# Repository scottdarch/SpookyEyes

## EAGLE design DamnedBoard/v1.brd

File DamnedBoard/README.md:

# Birds-of-the-Damned (say it in a spooky voice)

The hardware designs are provided under (Creative Commons Attribution-ShareAlike 3.0)[https://creativecommons.org/licenses/by-sa/3.0/legalcode].

The firmware is provided under Apache 2.0.

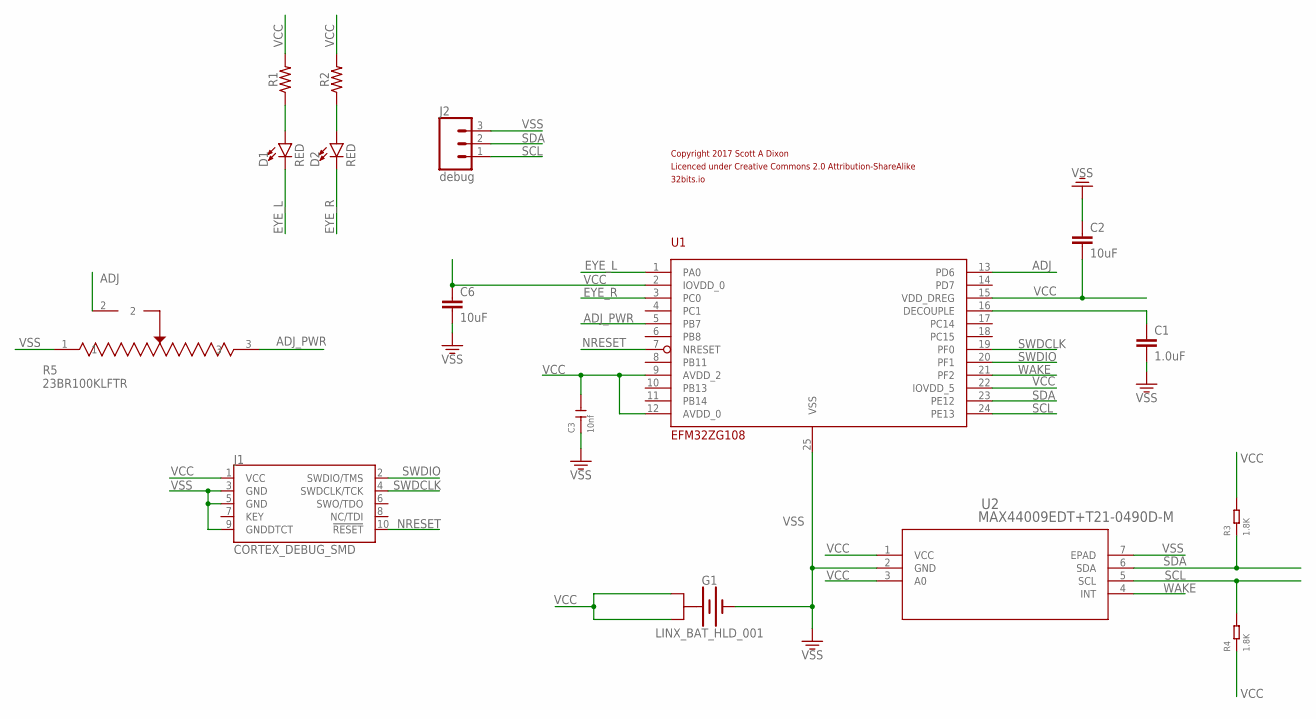
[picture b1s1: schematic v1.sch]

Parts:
C1: 1.0uF; 0603
C2, C6: 10uF; 0805
C3: 10nf; C0402
D1, D2: RED; LED-1206
G1: LINX_BAT_HLD_001; BATT-RETAINER-20MM
J1: CORTEX_DEBUG_SMD; SAMTECH_FTSH-105-01
J2: debug; 1X03
R1, R2: 68OHM-0603-1/10W-1%; 0603
R3, R4: 1.8K; R0402
R5: 23BR100KLFTR; SOT_23BR100KLFTR
U1: EFM32ZG108; QFN-24
U2: MAX44009EDT+T21-0490D-M; 21-0490D-M
U$1: COPYRIGHT

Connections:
ADJ: R5.2, U1.13 (PD6)
ADJ_PWR: R5.3, U1.5 (PB7)
DCP: C1.1, U1.16 (DECOUPLE)
EYE_L: D1.C, U1.1 (PA0)
EYE_R: D2.C, U1.3 (PC0)
unnamed: D2.A, R2.1
unnamed: D1.A, R1.1
NRESET: J1.10 (!RESET), U1.7 (NRESET)
SCL: J2.1, R4.2, U1.24 (PE13), U2.5 (SCL)
SDA: J2.2, R3.1, U1.23 (PE12), U2.6 (SDA)
SWDCLK: J1.4 (SWDCLK/TCK), U1.19 (PF0)
SWDIO: J1.2 (SWDIO/TMS), U1.20 (PF1)
VCC: C2.2, C3.2, C6.1, G1.P$1 (+$1), G1.P$2 (+$1), G1.P$3 (+$2), G1.P$4 (+$2), J1.1 (VCC), R1.2, R2.2, R3.2, R4.1, U1.2 (IOVDD_0), U1.9 (AVDD_2), U1.12 (AVDD_0), U1.15 (VDD_DREG), U1.22 (IOVDD_5), U2.1 (VCC), U2.3 (A0)
VSS: C1.2, C2.1, C3.1, C6.2, G1.P$0 (-), J1.3 (GND), J1.5 (GND), J1.9 (GNDDTCT), J2.3, R5.1, U1.25 (VSS), U2.2 (GND), U2.7 (EPAD)
WAKE: U1.21 (PF2), U2.4 (INT)

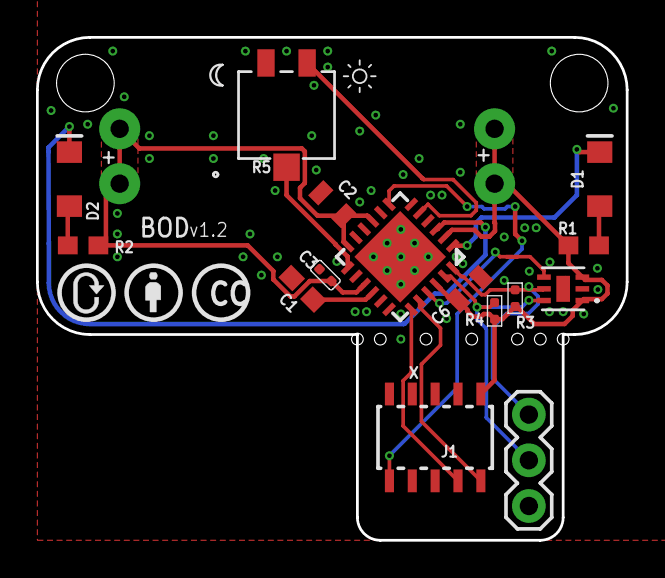
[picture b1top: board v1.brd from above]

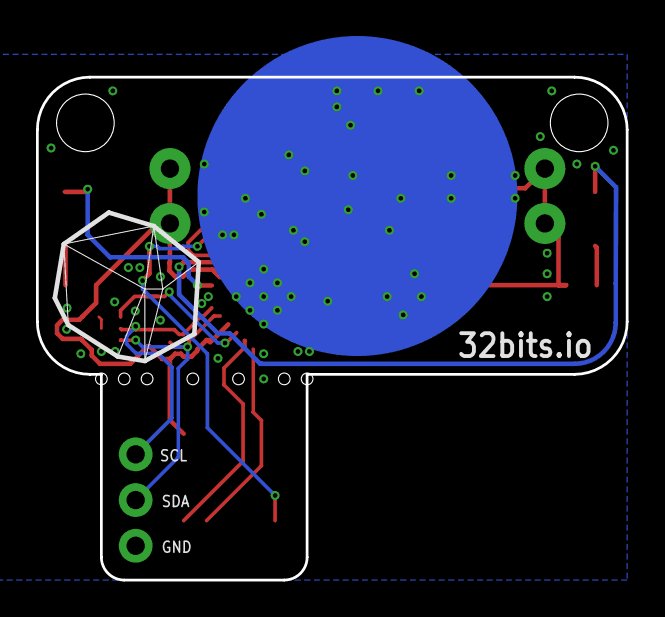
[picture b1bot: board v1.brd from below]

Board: 2 copper layers, 32.8 x 27.9 mm, 18 parts (2 on the bottom side), 15 nets.

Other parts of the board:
U$2: 32BITS_LOGO

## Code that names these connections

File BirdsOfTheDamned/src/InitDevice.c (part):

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
    // $[Port A Configuration]

    /* Pin PA0 is configured to Push-pull */
    GPIO->P[0].DOUT |= (1 << 0);
    GPIO->P[0].MODEL = (GPIO->P[0].MODEL & ~_GPIO_P_MODEL_MODE0_MASK)
            | GPIO_P_MODEL_MODE0_PUSHPULL;
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
    // $[Port C Configuration]

    /* Pin PC0 is configured to Push-pull */
    GPIO->P[2].DOUT |= (1 << 0);
    GPIO->P[2].MODEL = (GPIO->P[2].MODEL & ~_GPIO_P_MODEL_MODE0_MASK)
            | GPIO_P_MODEL_MODE0_PUSHPULL;
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
    // $[Port E Configuration]

    /* Pin PE12 is configured to Open-drain with pull-up and filter */
    GPIO->P[4].MODEH = (GPIO->P[4].MODEH & ~_GPIO_P_MODEH_MODE12_MASK)
            | GPIO_P_MODEH_MODE12_WIREDANDPULLUPFILTER;

    /* Pin PE13 is configured to Open-drain with pull-up and filter */
    GPIO->P[4].MODEH = (GPIO->P[4].MODEH & ~_GPIO_P_MODEH_MODE13_MASK)
            | GPIO_P_MODEH_MODE13_WIREDANDPULLUPFILTER;
    // [Port E Configuration]$

    // $[Port F Configuration]

    /* Pin PF2 is configured to Input enabled with pull-up */
    GPIO->P[5].DOUT |= (1 << 2);
    GPIO->P[5].MODEL = (GPIO->P[5].MODEL & ~_GPIO_P_MODEL_MODE2_MASK)
            | GPIO_P_MODEL_MODE2_INPUTPULL;
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
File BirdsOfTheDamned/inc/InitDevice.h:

//=========================================================
// inc/InitDevice.h: generated by Hardware Configurator
//
// This file will be regenerated when saving a document.
// leave the sections inside the "$[...]" comment tags alone
// or they will be overwritten!
//=========================================================
#ifndef __INIT_DEVICE_H__
#define __INIT_DEVICE_H__

// USER CONSTANTS
// USER PROTOTYPES

// $[Mode Transition Prototypes]
extern void enter_DefaultMode_from_RESET(void);
// [Mode Transition Prototypes]$

// $[Config(Per-Module Mode)Transition Prototypes]
extern void HFXO_enter_DefaultMode_from_RESET(void);
extern void LFXO_enter_DefaultMode_from_RESET(void);
extern void CMU_enter_DefaultMode_from_RESET(void);
extern void ADC0_enter_DefaultMode_from_RESET(void);
extern void ACMP0_enter_DefaultMode_from_RESET(void);
extern void IDAC0_enter_DefaultMode_from_RESET(void);
extern void RTC_enter_DefaultMode_from_RESET(void);
extern void USART1_enter_DefaultMode_from_RESET(void);
extern void LEUART0_enter_DefaultMode_from_RESET(void);
extern void VCMP_enter_DefaultMode_from_RESET(void);
extern void WDOG_enter_DefaultMode_from_RESET(void);
extern void I2C0_enter_DefaultMode_from_RESET(void);
extern void TIMER0_enter_DefaultMode_from_RESET(void);
extern void TIMER1_enter_DefaultMode_from_RESET(void);
extern void PCNT0_enter_DefaultMode_from_RESET(void);
extern void PRS_enter_DefaultMode_from_RESET(void);
extern void PORTIO_enter_DefaultMode_from_RESET(void);
// [Config(Per-Module Mode)Transition Prototypes]$

// $[User-defined pin name abstraction]

#define ADC0_CH6_PIN            (6)
#define ADC0_CH6_PORT           (gpioPortD)

#define ADJ_PIN                 (6)
#define ADJ_PORT                (gpioPortD)

#define ADJ_PWR_PIN             (11)
#define ADJ_PWR_PORT            (gpioPortB)

#define EYE_L_PIN               (0)
#define EYE_L_PORT              (gpioPortA)

#define EYE_R_PIN               (0)
#define EYE_R_PORT              (gpioPortC)

#define GPIO_EM4WU4_PIN         (2)
#define GPIO_EM4WU4_PORT        (gpioPortF)

#define I2C0_SCL_PIN            (13)
#define I2C0_SCL_PORT           (gpioPortE)

#define I2C0_SDA_PIN            (12)
#define I2C0_SDA_PORT           (gpioPortE)

#define LED0_PIN                (10)
#define LED0_PORT               (gpioPortC)

#define LED1_PIN                (11)
#define LED1_PORT               (gpioPortC)

#define TIMER0_CC0_PIN          (0)
#define TIMER0_CC0_PORT         (gpioPortA)

#define TIMER0_CC1_PIN          (0)
#define TIMER0_CC1_PORT         (gpioPortC)

#define WAKE_PIN                (2)
#define WAKE_PORT               (gpioPortF)

// [User-defined pin name abstraction]$

#endif

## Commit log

2015-10-19 Committing initial spooky.ino
2015-10-26 Version with watchdog sleep.
2015-10-26 Fixes daylight sleep mode.
2016-09-18 Starting on bitbang I2C for ATTiny10
2016-09-19 Incremental progress on bitbanged I2C.
2016-09-20 Simplified max44009 driver to fit in attiny10 code size.
2016-09-25 Attiny 10 didn't have pins. Sticking with ATTiny13a.
2016-10-13 Basically works at this change. Not much debugging though.
2016-10-21 Rough version with WDT sleeps.
2016-10-24 Handling interrupt properly now.
2016-10-25 Switching to low power 128k clock.
2017-08-22 Stubbing out v3 artifacts and branch.
2017-08-28 Start of v1 damned board.
2017-08-28 OSH Parkifying layout.
2017-08-29 Progress on layout.
2017-08-30 Candidate for manufacturing.
2017-09-02 Starting on new EFM32 firmware
2017-09-03 Added pullups to i2c
2017-09-04 V1.1 pinout with all tests points.
2017-09-04 Starting on software objects.
    v1.1 candidate for hardware as well.
2017-09-04 Progress on the adjustable version.
2017-09-05 Progress on v1.1
    Added trim pot to use for light threshold adjustment.
2017-09-10 Adding Yakindu machine for firmware.
2017-09-10 Hooking up real sensor logic. x; :x :x
2017-09-10 Working EM4 version of the firmware.
    Also increased pullups to 1.8K for lower power.
2017-09-11 Enabling wdtimer and fixing second eye.
2017-09-14 Moving to ADC for trimmer.
2017-09-18 V1.1 locked. Ordered from OSH park.
    All perphierals working in the firmware. Just need to finish some features and tune.
2017-09-24 Low power lurking implemented.
    TODO:
    1. Proper glow animation.
    2. Read trimpot and calibrate daylight sensor.
    3. Read ADC to get random seed.
    4. use rand to randomize lurk time.
2017-09-24 Adding custom pin names to CS config.
2017-09-25 Adding randomized lurk.
    TODO:
    1. Proper glow animation.
    2. Read trimpot and calibrate daylight sensor.
2017-09-26 Adding machine guided glow animation.
    1. Hookup the trimmer to daylight sensitivity.
    2. Fix the unknown energy draw during lurk.
2017-10-01 Adding 110F32 configuration and cleaning up old files.
2017-10-01 Hooking up ADC and trimpot.
2017-11-14 Adding scheatic png

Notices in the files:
BirdsOfTheDamned/src/InitDevice.c:
$[TIMER0 CC0 init]
$[TIMER1 CC0 init]
Enable signals CC0, CC1
parts and their libraries:
SparkFun-LED: Licensing: Creative Commons ShareAlike 4.0 International - https://creativecommons.org/licenses/by-sa/4.0
boneyard: Copyright 2017 Scott A Dixon
boneyard: Licenced under Creative Commons 2.0 Attribution-ShareAlike
